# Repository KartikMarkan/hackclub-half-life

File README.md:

# NovaSense!!!
NovaSense is my first ever PCB design project that I have ever made! I was so exicted to make this project, and I can't wait to solder it! This ReadMe will explain the whole process I went through. Before we start, I want to explain how the project works: If you press one button, random text appears("Hello"), and if you press the other button, the temaptrue appears on the OLED screen. 

## Hardware/Connections: 
### Components
- **Microcontroller**: xiao esp32-c3
- **Display**: SSD1306 128x64 OLED screen (I2C interface)
- **Sensor**: DHT11 Temperature/Humidity sensor
- **Buttons**: 2x momentary push buttons (SW1, SW2)
- **LED**: Status indicator LED

### Pin Configuration
| Component | Pin |
|-----------|-----|
| Left Button (SW1) | D2 |
| Right Button (SW2) | D3 |
| LED | D6 |
| DHT11 Sensor | D1 |
| OLED SDA | D5 |
| OLED SCL | D4 |

### I2C Address
- OLED Display: `0x3C`

## Software Stack

- **Language**: C++ (Arduino)
- **Display Library**: Adafruit GFX + Adafruit SSD1306
- **Sensor Library**: Adafruit DHT
- **Communication**: I2C (Wire.h)
- **Baud Rate**: 115200 (Serial debugging)

## Project Structure

## MY JOURNAL:
### 
Started My First PCB Project!!!!

I started off by following the Starbie PCB design.
I did this by first downloading the KiCad software on my computer and connecting it to GitHub. After that, I watched 5 minutes of a 30 min youtube (its called Beginner's Guide to PCB Design in 30 Minutes by Tinkering Techie). I followed along to the instructions, and it took me ten whole minutes(lol): 

My diagrm from the Youtube Tutorial: 

After watching the video, and checking voer everything, I decided to move on to the Starbie Tutorial from Half Life( Note: I am only using the tutorial to leanr before starting my actual PCB project). 

I started with the first step of getting the Seeed Studio XIAO ESP32-C3 connected to the other components, like the DHT11 moudel. After connecting everything based on the guide, I ran the ERC to check if anything was wrong. I foudn a few errors of the GNd, and 5V, but with chatgpt's help I was able to fix them. 

Here is a image of the schestamatic that follows the guide:

Now I added my own two componets: Led, and resitor.I rewired everything to get this: 

After checking again with ERC, I fixed all the warnings, and wiring problems with the help of some people in # Half Life Help 

Finally I got to work on my PCB design, and move on from the shcestamtic. I first went to the edge cut layer, and made my design: 
 
            - A baisc sqaure curved design with two buttons on the side, and holes in all corners. 
                 - Includes the LCD on the top, and LED in the middle. 

After fixing the issues, I routed my wires, and used DRC to check any mistakes (I got 25 wanrings, and 2 errors)

I fixed this through the help of Half life help. I asked many people, and they told me that i had 4 uncconeted wires(silly me)

I fixed those, and got 2 errors and 18 warnigns, just like the guide(so this means nothing is wrong)

Here is my final PCB design(withut routing wires):

Finally, I did a 3d editor view, and got this; 

After that, I went to Arduino IDE go start my coding. Most of my coding details are in my journal in Half Life.( i provided all the information about the code there)
      1. I added liabries
      2. CHanged port to microcontroller XIAO 
      3. Made the code so that when you press a button: a led might light up, the hummity cgets dispaly on LCD, or "Hello might be prinnted on LCD. 
Next I uploaded a desing of new york city as a small feature. After that, I uplaoded my desing into JLCPCB and customized it based on that. 

Thats all! 

ALSO NOTE: For the money/costs, this is a screen shot for PCb design, since i didn't know how to share it for costs. 

Pleaase choose direct global shipping, and this: 

BOM Table :

# Components and Cost

| Part | What it's for | Qty | Total ($) | Vendor |
|---|---|---:|---:|---|
| [Seeed Studio XIAO ESP32-C3](https://www.seeedstudio.com/Seeed-XIAO-ESP32C3-p-5431.html) | Used for the microcontrolelr and controlling everything! | 1 | 4.99 | [See Studio](https://www.seeedstudio.com/Seeed-XIAO-ESP32C3-p-5431.html) |
| [0.96-inch I²C OLED, 128×64](https://www.aliexpress.us/item/3256806179566773.html?src=google\&gatewayAdapt=glo2usa) | To dispaly the text, and hummity around the air. | 1 | 1.09 | [AliExpress](https://www.aliexpress.us/item/3256806179566773.html?src=google\&gatewayAdapt=glo2usa) |
| [MPU-6050 MPU6050](https://www.aliexpress.us/item/2251832613625365.html?utm_source=chatgpt.com\&oppcref=afc922b8-3e9e-4f01-9274-165692347f5a\&gatewayAdapt=4itemAdapt) | For Gyroscope | 1 | 1.09 | [AliExpress](https://www.aliexpress.us/item/2251832613625365.html?utm_source=chatgpt.com\&oppcref=afc922b8-3e9e-4f01-9274-165692347f5a\&gatewayAdapt=4itemAdapt) |
| [DHT11 Sensor](https://www.aliexpress.us/item/3256807193101859.html?spm=a2g0o.productlist.main.6.21c062a4L286ju\&algo_pvid=64ffd2c1-6f33-4a63-8077-6ad4980d00e8\&algo_exp_id=64ffd2c1-6f33-4a63-8077-6ad4980d00e8-5\&pdp_ext_f=%7B%22order%22%3A%2217%22%2C%22eval%22%3A%221%22%2C%22fromPage%22%3A%22search%22%7D\&pdp_npi=6%40dis%21USD%211.84%211.09%21%21%211.84%211.09%21%402101d33417917508270772336e11df%2112000040495726382%21sea%21US%210%21ABX%211%210%21n_tag%3A-29910%3Bd%3Aeb5bcb9b%3Bm03_new_user%3A-29895%3BpisId%3A5000000218165385\&curPageLogUid=rmCwzObMgEk0\&utparam-url=scene%3Asearch%7Cquery_from%3A%7Cx_object_id%3A1005007379416611%7C_p_origin_prod%3A) | Used to display temperature. | 1 | 1.09 | [AliExpress](https://www.aliexpress.us/item/3256807193101859.html?spm=a2g0o.productlist.main.6.21c062a4L286ju\&algo_pvid=64ffd2c1-6f33-4a63-8077-6ad4980d00e8\&algo_exp_id=64ffd2c1-6f33-4a63-8077-6ad4980d00e8-5\&pdp_ext_f=%7B%22order%22%3A%2217%22%2C%22eval%22%3A%221%22%2C%22fromPage%22%3A%22search%22%7D\&pdp_npi=6%40dis%21USD%211.84%211.09%21%21%211.84%211.09%21%402101d33417917508270772336e11df%2112000040495726382%21sea%21US%210%21ABX%211%210%21n_tag%3A-29910%3Bd%3Aeb5bcb9b%3Bm03_new_user%3A-29895%3BpisId%3A5000000218165385\&curPageLogUid=rmCwzObMgEk0\&utparam-url=scene%3Asearch%7Cquery_from%3A%7Cx_object_id%3A1005007379416611%7C_p_origin_prod%3A) |
| [PCB Part](https://cart.jlcpcb.com/quote?spm=jlcpcb.Public.2006\&spm=Jlcpcb.Instantquote&_t=1791753237824\&up_spm=Jlcpcb.Loginpage.1003) | The main board, also idk how to upload this, so I put my files on github, and took a screenshot for the person buying it! The shipping should be through Gloabl direct which is $7. | 1 | 4.00 | [JLCPCB](https://cart.jlcpcb.com/quote?spm=jlcpcb.Public.2006\&spm=Jlcpcb.Instantquote&_t=1791753237824\&up_spm=Jlcpcb.Loginpage.1003) |
| [Cherry MX-compatible switch](https://www.aliexpress.us/item/3256808470402926.html?spm=a2g0o.cart.0.0.404238dagG5YPF\&mp=1\&pdp_npi=6%40dis%21USD%21USD+7.52%21USD+1.09%21%21USD+1.09%21%21%21%402101d9ef17917538577586282e0d92%2112000046120217083%21ct%21US%21-1%21%211%210%21&_gl=1*18szfre*_gcl_aw*R0NMLjE3OTE3NTM2OTIuQ2p3S0NBanc1NnpXQmhCMEVpd0FkUE9RT2Q3VTU2aDJkVGdMdzExZjh0dEo2TlhGbGVsWHM1UUhCWnpERlNId18tV3A0YVp4RXVyRDZCb0NSMWtRQXZEX0J3RQ..*_gcl_dc*R0NMLjE3OTE3NTM2OTIuQ2p3S0NBanc1NnpXQmhCMEVpd0FkUE9RT2Q3VTU2aDJkVGdMdzExZjh0dEo2TlhGbGVsWHM1UUhCWnpERlNId18tV3A0YVp4RXVyRDZCb0NSMWtRQXZEX0J3RQ..*_gcl_au*MjI5NTY3MjU1LjE3OTE3NTM2OTI.*_ga*ODc4NTE0MzMzMTcwMTgxLjE3OTE3NTAzNDk2Mzk.*_ga_VED1YSGNC7*czE3OTE3NTM2OTEkbzEkZzEkdDE3OTE3NTM4MzIkajIzJGwwJGgw\&gatewayAdapt=glo2usa) | Used for pressing buttons | 1 | 1.09 | [Aliexpress](https://www.aliexpress.us/item/3256808470402926.html?spm=a2g0o.cart.0.0.404238dagG5YPF\&mp=1\&pdp_npi=6%40dis%21USD%21USD+7.52%21USD+1.09%21%21USD+1.09%21%21%21%402101d9ef17917538577586282e0d92%2112000046120217083%21ct%21US%21-1%21%211%210%21&_gl=1*18szfre*_gcl_aw*R0NMLjE3OTE3NTM2OTIuQ2p3S0NBanc1NnpXQmhCMEVpd0FkUE9RT2Q3VTU2aDJkVGdMdzExZjh0dEo2TlhGbGVsWHM1UUhCWnpERlNId18tV3A0YVp4RXVyRDZCb0NSMWtRQXZEX0J3RQ..*_gcl_dc*R0NMLjE3OTE3NTM2OTIuQ2p3S0NBanc1NnpXQmhCMEVpd0FkUE9RT2Q3VTU2aDJkVGdMdzExZjh0dEo2TlhGbGVsWHM1UUhCWnpERlNId18tV3A0YVp4RXVyRDZCb0NSMWtRQXZEX0J3RQ..*_gcl_au*MjI5NTY3MjU1LjE3OTE3NTM2OTI.*_ga*ODc4NTE0MzMzMTcwMTgxLjE3OTE3NTAzNDk2Mzk.*_ga_VED1YSGNC7*czE3OTE3NTM2OTEkbzEkZzEkdDE3OTE3NTM4MzIkajIzJGwwJGgw\&gatewayAdapt=glo2usa) |
| [Keycaps](https://www.aliexpress.us/item/3256811960232273.html?spm=a2g0o.productlist.main.2.23be12036QkBbX\&algo_pvid=a460f664-6d0f-4f7c-ada0-091779c90ee6\&algo_exp_id=a460f664-6d0f-4f7c-ada0-091779c90ee6-1\&pdp_ext_f=%7B%22order%22%3A%22938%22%2C%22eval%22%3A%221%22%2C%22fromPage%22%3A%22search%22%7D\&pdp_npi=6%40dis%21GBP%212.76%211.76%21%21%213.53%212.25%21%402103956a17911049055707941e1490%2112000057621889504%21sea%21UK%210%21ABX%211%210%21n_tag%3A-29910%3Bd%3Af20e294%3Bm03_new_user%3A-29895%3BpisId%3A5000000218658082\&curPageLogUid=KP8wqdHZI0jA\&utparam-url=scene%3Asearch%7Cquery_from%3A%7Cx_object_id%3A1005012146547025%7C_p_origin_prod%3A\&gatewayAdapt=glo2usa4itemAdapt) | For the buttons to press on (only need the 10 pack since cheapest) | 1 | 1.09 | [Aliexpress](https://www.aliexpress.us/item/3256811960232273.html?spm=a2g0o.productlist.main.2.23be12036QkBbX\&algo_pvid=a460f664-6d0f-4f7c-ada0-091779c90ee6\&algo_exp_id=a460f664-6d0f-4f7c-ada0-091779c90ee6-1\&pdp_ext_f=%7B%22order%22%3A%22938%22%2C%22eval%22%3A%221%22%2C%22fromPage%22%3A%22search%22%7D\&pdp_npi=6%40dis%21GBP%212.76%211.76%21%21%213.53%212.25%21%402103956a17911049055707941e1490%2112000057621889504%21sea%21UK%210%21ABX%211%210%21n_tag%3A-29910%3Bd%3Af20e294%3Bm03_new_user%3A-29895%3BpisId%3A5000000218658082\&curPageLogUid=KP8wqdHZI0jA\&utparam-url=scene%3Asearch%7Cquery_from%3A%7Cx_object_id%3A1005012146547025%7C_p_origin_prod%3A\&gatewayAdapt=glo2usa4itemAdapt) |
| 10k resitor&#x20; | For transferring power/controlling power | 1 | 1.09 | [Aliexpress](https://www.aliexpress.us/item/3256801782956510.html?spm=a2g0o.detail.0.0.16a0EHemEHemva\&mp=1\&pdp_npi=6%40dis%21USD%21USD+3.52%21USD+1.09%21%21USD+1.09%21%21%21%402101d3fe17929801363494562e0d28%2112000018268283437%21ct%21US%216215269144%21%211%210%21&_gl=1*11n3lcm*_gcl_aw*R0NMLjE3OTE3NzEwODQuQ2p3S0NBanc1NnpXQmhCMEVpd0FkUE9RT1lLUVFMNmRTSGlRUFl1bFVEeFVHVldmX2Mxa1FZZ1AtYmFNTGZvMElpajkzM0hMSWFOamhCb0NGa1VRQXZEX0J3RQ..*_gcl_dc*R0NMLjE3OTE3NTM2OTIuQ2p3S0NBanc1NnpXQmhCMEVpd0FkUE9RT2Q3VTU2aDJkVGdMdzExZjh0dEo2TlhGbGVsWHM1UUhCWnpERlNId18tV3A0YVp4RXVyRDZCb0NSMWtRQXZEX0J3RQ..*_gcl_au*MjI5NTY3MjU1LjE3OTE3NTM2OTI.*_ga*MTQyNzU0MDA1Ny4xNzkyOTgwMDgy*_ga_VED1YSGNC7*czE3OTI5ODAwODEkbzEkZzEkdDE3OTI5ODAxMzYkajUkbDAkaDA.\&gatewayAdapt=glo2usa) |
| LEDS | For lighting up when button pressed | 1 | 5.04 | [Aliexpress](https://www.aliexpress.us/item/3256803133826213.html?spm=a2g0o.productlist.main.4.7dd5648e9gJHMH\&aem_p4p_detail=202610261629328916696654775920000275276\&algo_pvid=e6b4c795-8cfc-4e7d-b19c-4495f5f9c3b2\&algo_exp_id=e6b4c795-8cfc-4e7d-b19c-4495f5f9c3b2-3\&pdp_ext_f=%7B%22order%22%3A%22818%22%2C%22eval%22%3A%221%22%2C%22fromPage%22%3A%22search%22%7D\&pdp_npi=6%40dis%21USD%214.06%211.09%21%21%214.06%211.09%21%402101ef5e17930573728131574e0fcd%2112000025195201401%21sea%21US%216215269144%21ACX%211%210%21n_tag%3A-29919%3Bd%3Aeb5bcb9b%3Bm03_new_user%3A-29894%3BpisId%3A5000000218161405\&curPageLogUid=8aScn0lHstH8\&utparam-url=scene%3Asearch%7Cquery_from%3A%7Cx_object_id%3A1005003320140965%7C_p_origin_prod%3A\&search_p4p_id=202610261629328916696654775920000275276_1) |
| Tax & shipping |  |  | 8 |  |
| Total |  |  | 28.57 |  |

**Estimated total: $28.57**

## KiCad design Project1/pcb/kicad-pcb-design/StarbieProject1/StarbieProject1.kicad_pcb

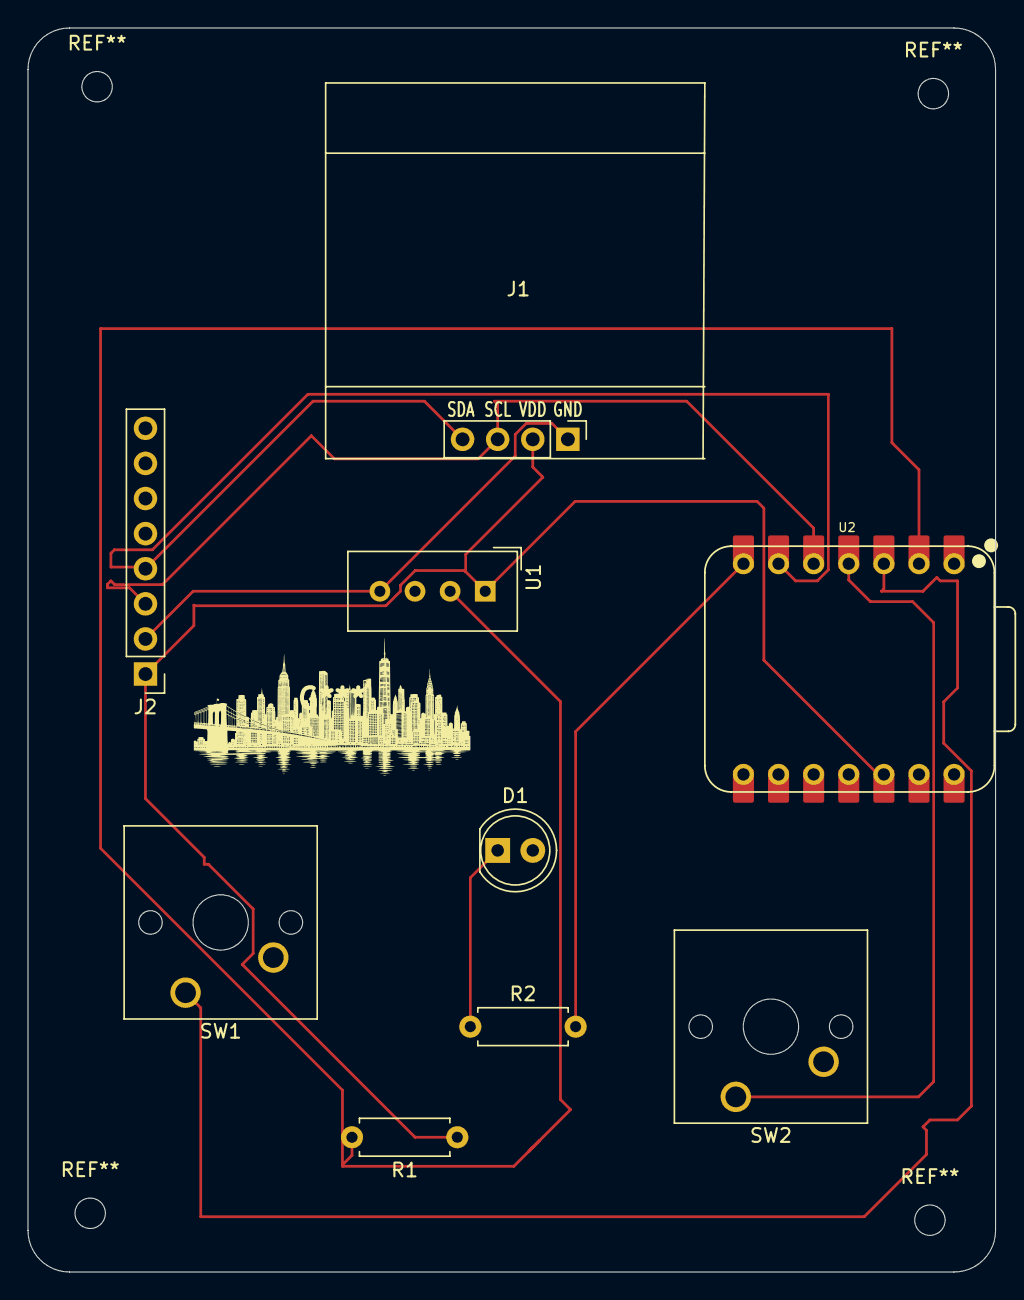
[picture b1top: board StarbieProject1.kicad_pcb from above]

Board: 2 copper layers, 70.0 x 90.0 mm, 9 parts (0 on the bottom side), 9 nets.

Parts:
D1: LED; LED_D5.0mm
J1: Conn_01x04_Pin; Imported Display_128x64_096_I2C
J2: Conn_01x08_Pin; PinHeader_1x08_P2.54mm_Vertical
R1: 10k; R_Axial_DIN0207_L6.3mm_D2.5mm_P7.62mm_Horizontal
R2: 1k; R_Axial_DIN0207_L6.3mm_D2.5mm_P7.62mm_Horizontal
SW1, SW2: SW_Push; SW_Cherry_MX_1.00u_PCB
U1: DHT11; Aosong_DHT11_5.5x12.0_P2.54mm
U2: XIAO-ESP32-C3-SMD; XIAO-ESP32-C6-DIP

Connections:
+3.3V: J1.2, J2.1, R1.1, U1.1 (VDD), U2.12 (3V3_OUT)
/DHT11 DATA: R1.2, U1.2 (DATA), U2.2 (D1)
/GPIO2: SW1.1, U2.3 (D2)
/GPIO3: SW2.1, U2.4 (D3)
/SCL: J1.3, J2.3, U2.5 (D4)
/SDA: J1.4, J2.4, U2.6 (D5)
GND: D1.2 (A), J1.1, J2.2, SW1.2, SW2.2, U1.4 (GND), U2.13 (GND)
unnamed: D1.1 (K), R2.1
unnamed: R2.2, U2.7 (D6)
